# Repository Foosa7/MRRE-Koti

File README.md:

# MRRE-Koti #
* CERN Open Hardware Licence v1.2 
* Original: https://github.com/maplerainresearch/MRR_ESPE

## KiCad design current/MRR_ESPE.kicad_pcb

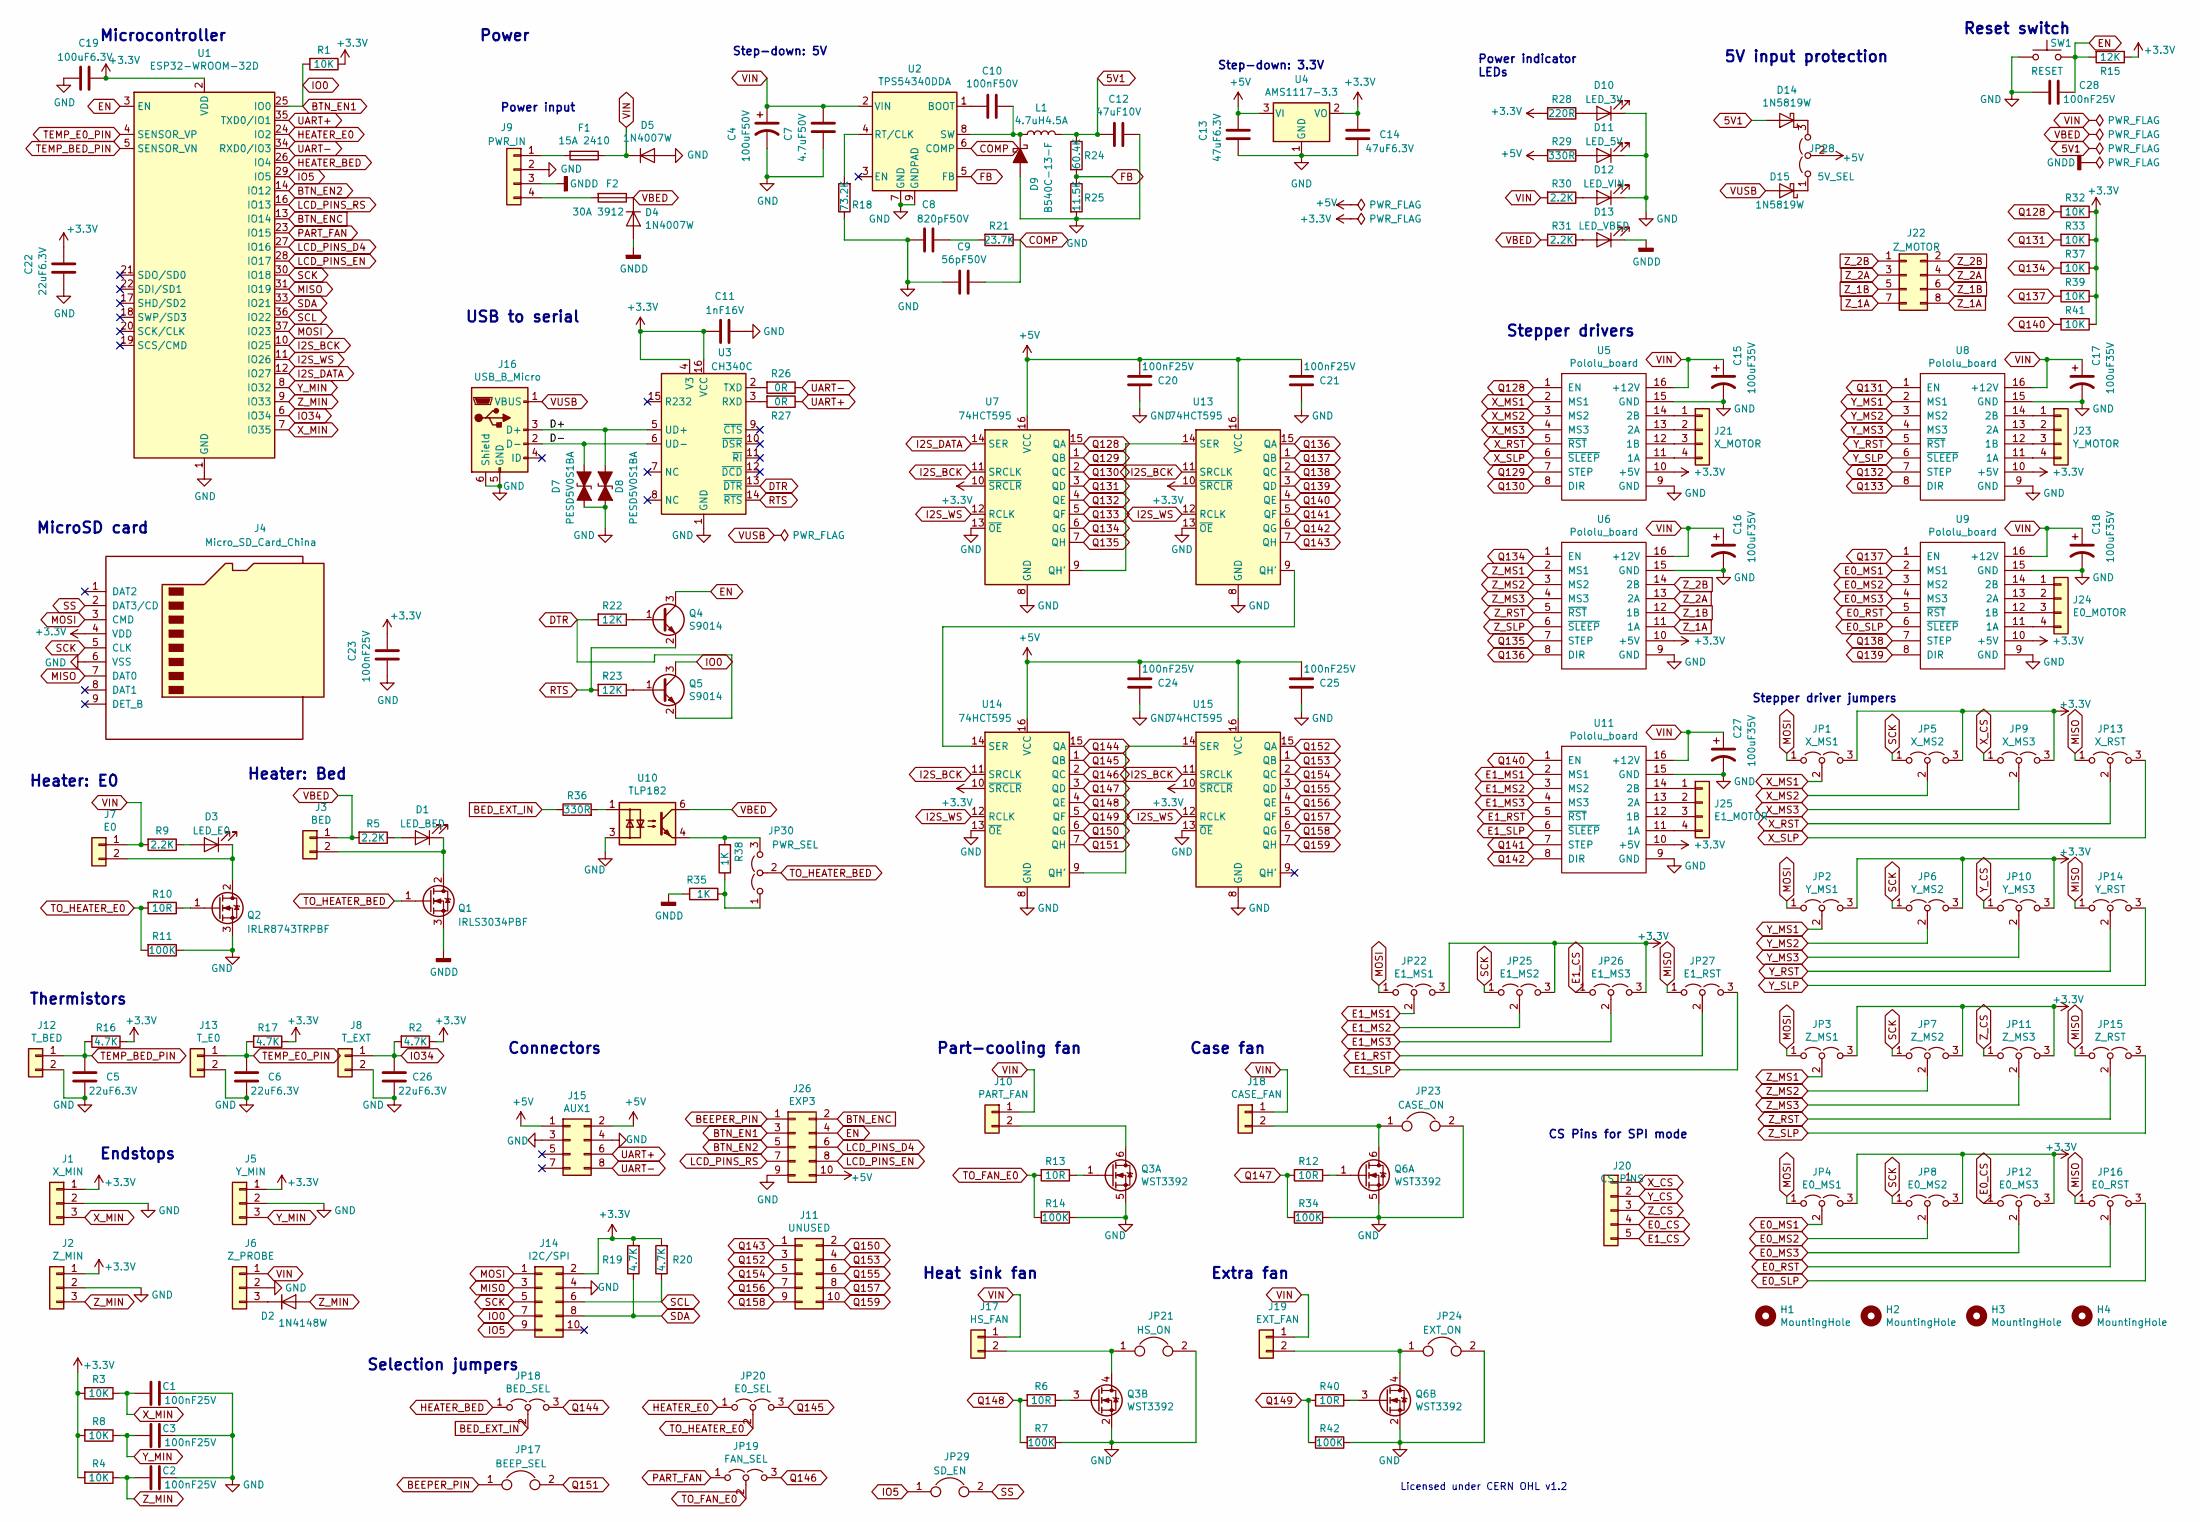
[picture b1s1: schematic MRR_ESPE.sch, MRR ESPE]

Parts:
C1, C2, C3, C20, C21, C23, C24, C25, C28: 100nF25V; C_0805_2012Metric; Mfg part no. 0805B104K250; LCSC Part Number C128353
C4: 100uF50V; CP_Elec_8x10; Mfg part no. VEJ101M1HTR-0810; LCSC Part Number C176665
C5, C6, C22, C26: 22uF6.3V; C_0805_2012Metric; Mfg part no. CL21A226MQQNNNE; LCSC Part Number C5674
C7: 4.7uF50V; C_1206_3216Metric; Mfg part no. CL31B475KBHNFNE; LCSC Part Number C307575
C8: 820pF50V; C_0805_2012Metric; Mfg part no. 0805B821K500CT; LCSC Part Number C152862
C9: 56pF50V; C_0805_2012Metric; Mfg part no. 0805N560J500CT; LCSC Part Number C296102
C10: 100nF50V; C_0805_2012Metric; Mfg part no. GCM21BR71H104KA37L; LCSC Part Number C161260
C11: 1nF16V; C_0805_2012Metric; Mfg part no. 0805B103K500NT; LCSC Part Number C52278
C12: 47uF10V; C_1206_3216Metric; Mfg part no. LMK316BJ476ML-T; LCSC Part Number C92821
C13, C14: 47uF6.3V; C_0805_2012Metric; Mfg part no. JMK212BJ476MG-T; LCSC Part Number C87159
C15, C16, C17, C18, C27: 100uF35V; CP_Elec_6.3x7.7; Mfg part no. CS1V101M-CRE77; LCSC Part Number C97811
C19: 100uF6.3V; C_1206_3216Metric; Mfg part no. CL31A107MQHNNNE; LCSC Part Number C15008
D1: LED_BED; LED_0805; Mfg part no. 17-21SURC/S530-A3/TR8; LCSC Part Number C72037
D2: 1N4148W; D_SOD-123; Mfg part no. 1N4148W; LCSC Part Number C81598
D3: LED_E0; LED_0805; Mfg part no. 17-21SURC/S530-A3/TR8; LCSC Part Number C72037
D4, D5: 1N4007W; D_SOD-123F; Mfg part no. 1N4007W; LCSC Part Number C108803
D7, D8: PESD5V0S1BA; D_SOD-323; Mfg part no. PESD5V0S1BA,115; LCSC Part Number C19224
D9: B540C-13-F; D_SMC; Mfg part no. B540C-13-F; LCSC Part Number C72264
D10: LED_3V; LED_0805; Mfg part no. 17-21SYGC/S530-E2/TR8; LCSC Part Number C73548
D11: LED_5V; LED_0805; Mfg part no. 17-21SYGC/S530-E2/TR8; LCSC Part Number C73548
D12: LED_VIN; LED_0805; Mfg part no. 17-21/BHC-XL2M2TY/3T; LCSC Part Number C72035
D13: LED_VBED; LED_0805; Mfg part no. 17-21/BHC-XL2M2TY/3T; LCSC Part Number C72035
D14, D15: 1N5819W; D_SOD-123; Mfg part no. 1N5819W; LCSC Part Number C169540
F1: 15A 2410; Littelfuse_0451; Mfg part no. 0451015.MRL; LCSC Part Number C44480
F2: 30A 3912; Littelfuse_0456; Mfg part no. 0456030.ER; LCSC Part Number C187558
H1, H2, H3, H4: MountingHole; MountingHole_3.2mm_M3_DIN965
J1: X_MIN; JST_XH_B03B-XH-A_1x03_P2.50mm_Vertical; Mfg part no. B3B-XH-A(LF)(SN); LCSC Part Number C144394
J2: Z_MIN; JST_XH_B03B-XH-A_1x03_P2.50mm_Vertical; Mfg part no. B3B-XH-A(LF)(SN); LCSC Part Number C144394
J3: BED; TerminalBlock_Phoenix_MKDS-3-2-5.08_1x02_P5.08mm_Horizontal; Mfg part no. MKDS3/2-5.08; LCSC Part Number C89120
J4: Micro_SD_Card_China; Koti_uSDcard; Mfg part no. TF-15×15; LCSC Part Number C111196
J5: Y_MIN; JST_XH_B03B-XH-A_1x03_P2.50mm_Vertical; Mfg part no. B3B-XH-A(LF)(SN); LCSC Part Number C144394
J6: Z_PROBE; JST_XH_B03B-XH-A_1x03_P2.50mm_Vertical; Mfg part no. B3B-XH-A(LF)(SN); LCSC Part Number C144394
J7: E0; TerminalBlock_Phoenix_MKDS-1,5-2-5.08_1x02_P5.08mm_Horizont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; Mfg part no. MKDSN1.5/2-5.08; LCSC Part Number C91153
J8: T_EXT; PinHeader_1x02_P2.54mm_Vertical; Mfg part no. C124375; LCSC Part Number C124375
J9: PWR_IN; TerminalBlock_Phoenix_MKDS-3-4-5.08_1x04_P5.08mm_Horizontal; Mfg part no. MKDS3/4-5.08; LCSC Part Number C90087
J10: PART_FAN; PinHeader_1x02_P2.54mm_Vertical; Mfg part no. C124375; LCSC Part Number C124375
J11: UNUSED; PinHeader_2x05_P2.54mm_Vertical; Mfg part no. C124387; LCSC Part Number C124387
J12: T_BED; PinHeader_1x02_P2.54mm_Vertical; Mfg part no. C124375; LCSC Part Number C124375
J13: T_E0; PinHeader_1x02_P2.54mm_Vertical; Mfg part no. C124375; LCSC Part Number C124375
J14: I2C/SPI; PinHeader_2x05_P2.54mm_Vertical; Mfg part no. C124387; LCSC Part Number C124387
J15: AUX1; IDC-Header_2x04_P2.54mm_Vertical; Mfg part no. C9135; LCSC Part Number C9135
J16: USB_B_Micro; USB_Micro-B_Molex-105017-0001; Mfg part no. 105017-0001; LCSC Part Number C136000
J17: HS_FAN; PinHeader_1x02_P2.54mm_Vertical; Mfg part no. C124375; LCSC Part Number C124375
J18: CASE_FAN; PinHeader_1x02_P2.54mm_Vertical; Mfg part no. C124375; LCSC Part Number C124375
J19: EXT_FAN; PinHeader_1x02_P2.54mm_Vertical; Mfg part no. C124375; LCSC Part Number C124375
J20: CS_PINS; PinHeader_1x05_P2.54mm_Vertical; Mfg part no. C124379; LCSC Part Number C124379
J21: X_MOTOR; PinHeader_1x04_P2.54mm_Vertical; Mfg part no. C124378; LCSC Part Number C124378
J22: Z_MOTOR; PinHeader_2x04_P2.54mm_Vertical; Mfg part no. C124386; LCSC Part Number C124386
J23: Y_MOTOR; PinHeader_1x04_P2.54mm_Vertical; Mfg part no. C124378; LCSC Part Number C124378
J24: E0_MOTOR; PinHeader_1x04_P2.54mm_Vertical; Mfg part no. C124378; LCSC Part Number C124378
J25: E1_MOTOR; PinHeader_1x04_P2.54mm_Vertical; Mfg part no. C124378; LCSC Part Number C124378
J26: EXP3; IDC-Header_2x05_P2.54mm_Vertical; Mfg part no. C5665; LCSC Part Number C5665
JP1: X_MS1; PinHeader_1x03_P2.54mm_Vertical; Mfg part no. C124376; LCSC Part Number C124376
JP2: Y_MS1; PinHeader_1x03_P2.54mm_Vertical; Mfg part no. C124376; LCSC Part Number C124376
JP3: Z_MS1; PinHeader_1x03_P2.54mm_Vertical; Mfg part no. C124376; LCSC Part Number C124376
JP4: E0_MS1; PinHeader_1x03_P2.54mm_Vertical; Mfg part no. C124376; LCSC Part Number C124376
JP5: X_MS2; PinHeader_1x03_P2.54mm_Vertical; Mfg part no. C124376; LCSC Part Number C124376
JP6: Y_MS2; PinHeader_1x03_P2.54mm_Vertical; Mfg part no. C124376; LCSC Part Number C124376
JP7: Z_MS2; PinHeader_1x03_P2.54mm_Vertical; Mfg part no. C124376; LCSC Part Number C124376
JP8: E0_MS2; PinHeader_1x03_P2.54mm_Vertical; Mfg part no. C124376; LCSC Part Number C124376
JP9: X_MS3; PinHeader_1x03_P2.54mm_Vertical; Mfg part no. C124376; LCSC Part Number C124376
JP10: Y_MS3; PinHeader_1x03_P2.54mm_Vertical; Mfg part no. C124376; LCSC Part Number C124376
JP11: Z_MS3; PinHeader_1x03_P2.54mm_Vertical; Mfg part no. C124376; LCSC Part Number C124376
JP12: E0_MS3; PinHeader_1x03_P2.54mm_Vertical; Mfg part no. C124376; LCSC Part Number C124376
JP13: X_RST; PinHeader_1x03_P2.54mm_Vertical; Mfg part no. C124376; LCSC Part Number C124376
JP14: Y_RST; PinHeader_1x03_P2.54mm_Vertical; Mfg part no. C124376; LCSC Part Number C124376
JP15: Z_RST; PinHeader_1x03_P2.54mm_Vertical; Mfg part no. C124376; LCSC Part Number C124376
JP16: E0_RST; PinHeader_1x03_P2.54mm_Vertical; Mfg part no. C124376; LCSC Part Number C124376
JP17: BEEP_SEL; PinHeader_1x02_P2.54mm_Vertical; Mfg part no. C124375; LCSC Part Number C124375
JP18: BED_SEL; PinHeader_1x03_P2.54mm_Vertical; Mfg part no. C124376; LCSC Part Number C124376
JP19: FAN_SEL; PinHeader_1x03_P2.54mm_Vertical; Mfg part no. C124376; LCSC Part Number C124376
JP20: E0_SEL; PinHeader_1x03_P2.54mm_Vertical; Mfg part no. C124376; LCSC Part Number C124376
JP21: HS_ON; PinHeader_1x02_P2.54mm_Vertical; Mfg part no. C124375; LCSC Part Number C124375
JP22: E1_MS1; PinHeader_1x03_P2.54mm_Vertical; Mfg part no. C124376; LCSC Part Number C124376
JP23: CASE_ON; PinHeader_1x02_P2.54mm_Vertical; Mfg part no. C124375; LCSC Part Number C124375
JP24: EXT_ON; PinHeader_1x02_P2.54mm_Vertical; Mfg part no. C124375; LCSC Part Number C124375
JP25: E1_MS2; PinHeader_1x03_P2.54mm_Vertical; Mfg part no. C124376; LCSC Part Number C124376
JP26: E1_MS3; PinHeader_1x03_P2.54mm_Vertical; Mfg part no. C124376; LCSC Part Number C124376
JP27: E1_RST; PinHeader_1x03_P2.54mm_Vertical; Mfg part no. C124376; LCSC Part Number C124376
JP28: 5V_SEL; PinHeader_1x03_P2.54mm_Vertical; Mfg part no. C124376; LCSC Part Number C124376
JP29: SD_EN; PinHeader_1x02_P2.54mm_Vertical; Mfg part no. C124375; LCSC Part Number C124375
JP30: PWR_SEL; PinHeader_1x03_P2.54mm_Vertical; Mfg part no. C124376; LCSC Part Number C124376
L1: 4.7uH4.5A; SMMS0530; Mfg part no. SMMS0530-4R7M; LCSC Part Number C181722
Q1: IRLS3034PBF; TO-263-2
Q2: IRLR8743TRPBF; TO-252-2
Q3, Q6: WST3392; SOT-23-6_Handsoldering; Mfg part no. WST3392; LCSC Part Number C148366
Q4, Q5: S9014; SOT-23; Mfg part no. S9014; LCSC Part Number C181164
R1, R3, R4, R8, R32, R33, R37, R39, R41: 10K; R_0805_2012Metric; Mfg part no. 0805W8F1002T5E; LCSC Part Number C38522
R2, R16, R17, R19, R20: 4.7K; R_0805_2012Metric; Mfg part no. 0805W8F4701T5E; LCSC Part Number C17673
R5, R9, R30, R31: 2.2K; R_0805_2012Metric; Mfg part no. 0805W8F2201T5E; LCSC Part Number C17520
R6, R10, R12, R13, R40: 10R; R_0805_2012Metric; Mfg part no. 0805W8F100JT5E; LCSC Part Number C17415
R7, R11, R14, R34, R42: 100K; R_0805_2012Metric; Mfg part no. 0805W8F1003T5E; LCSC Part Number C149504
R15, R22, R23: 12K; R_0805_2012Metric; Mfg part no. 0805W8F1202T5E; LCSC Part Number C17444
R18: 73.2K; R_0805_2012Metric; Mfg part no. WR08X7322FTL; LCSC Part Number C170958
R21: 23.7K; R_0805_2012Metric; Mfg part no. WR08X2372FTL; LCSC Part Number C170848
R24: 60.4K; R_0805_2012Metric; Mfg part no. RC0805FR-0760K4L; LCSC Part Number C273994
R25: 11.5K; R_0805_2012Metric; Mfg part no. 0805W8F1152T5E; LCSC Part Number C17418
R26, R27: 0R; R_0805_2012Metric; Mfg part no. 0805W8F0000T5E; LCSC Part Number C17477
R28: 220R; R_0805_2012Metric; Mfg part no. 0805W8F2200T5E; LCSC Part Number C17557
R29, R36: 330R; R_0805_2012Metric; Mfg part no. 0805W8F3300T5E; LCSC Part Number C17630
R35, R38: 1K; R_0805_2012Metric; Mfg part no. 0805W8F1001T5E; LCSC Part Number C17513
SW1: RESET; 6x6mmTactileSwitch; Mfg part no. K2-6639SP-C4SC-04; LCSC Part Number C83206
U1: ESP32-WROOM-32D; ESP32-WROOM-32; Mfg part no. ESP32-WROOM-32; LCSC Part Number C95209
U2: TPS54340DDA; TI_SO-PowerPAD-8_ThermalVias; Mfg part no. TPS54340DDAR; LCSC Part Number C45886
U3: CH340C; SOIC-16_3.9x9.9mm_P1.27mm; Mfg part no. CH340C; LCSC Part Number C84681
U4: AMS1117-3.3; SOT-223-3_TabPin2; Mfg part no. AMS1117-3.3; LCSC Part Number C6186
U5, U6, U8, U9, U11: Pololu_board; Pololu_Breakout-16_15.2x20.3mm; Mfg part no. x2; LCSC Part Number C27438
U7, U13, U14, U15: 74HCT595; TSSOP-16_4.4x5mm_P0.65mm; Mfg part no. MC74HCT595ADTR2G; LCSC Part Number C152276
U10: TLP182; MFSOP6-4_4.4x3.6mm_P1.27mm; Mfg part no. TLP182(GB-TPL,E; LCSC Part Number C96457

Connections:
5V1: C12.2, D14.2 (A), L1.2, R24.1
+3V3: C11.2, C14.1, C19.1, C22.1, C23.1, J1.1, J2.1, J4.4 (VDD), J5.1, J14.2, JP1.3 (B), JP2.3 (B), JP3.3 (B), JP4.3 (B), JP5.3 (B), JP6.3 (B), JP7.3 (B), JP8.3 (B), JP9.3 (B), JP10.3 (B), JP11.3 (B), JP12.3 (B), JP22.3 (B), JP25.3 (B), JP26.3 (B), R1.1, R2.1, R3.2, R4.2, R8.2, R15.1, R16.1, R17.1, R19.2, R20.2, R28.2, R32.1, R33.1, R37.1, R39.1, R41.1, U1.2 (VDD), U3.4 (V3), U3.16 (VCC), U4.2 (VO), U5.10 (+5V), U6.10 (+5V), U7.10 (~SRCLR), U8.10 (+5V), U9.10 (+5V), U11.10 (+5V), U13.10 (~SRCLR), U14.10 (~SRCLR), U15.10 (~SRCLR)
+5V: C13.1, C20.2, C21.2, C24.2, C25.2, J15.1, J15.2, J26.10, JP28.2 (C), R29.2, U4.3 (VI), U7.16 (VCC), U13.16 (VCC), U14.16 (VCC), U15.16 (VCC)
/D+: D8.1 (A1), J16.3 (D+), U3.5 (UD+)
/D-: D7.1 (A1), J16.2 (D-), U3.6 (UD-)
BED_EXT_IN: JP18.2 (C), R36.1
BEEPER_PIN: J26.1, JP17.1
BTN_EN1: J14.7, J26.3, Q5.3 (C), R1.2, U1.25 (IO0)
BTN_EN2: J26.5, U1.14 (IO12)
BTN_ENC: J26.2, U1.13 (IO14)
COMP: C9.1, R21.1, U2.6 (COMP)
DTR: Q5.2 (E), R22.2, U3.13 (~DTR)
E0_CS: J20.4, JP12.1 (A)
E0_MS1: JP4.2 (C), U9.2 (MS1)
E0_MS2: JP8.2 (C), U9.3 (MS2)
E0_MS3: JP12.2 (C), U9.4 (MS3)
E0_RST: JP16.2 (C), U9.5 (~RST)
E0_SLP: JP16.3 (B), U9.6 (~SLEEP)
E1_CS: J20.5, JP26.1 (A)
E1_MS1: JP22.2 (C), U11.2 (MS1)
E1_MS2: JP25.2 (C), U11.3 (MS2)
E1_MS3: JP26.2 (C), U11.4 (MS3)
E1_RST: JP27.2 (C), U11.5 (~RST)
E1_SLP: JP27.3 (B), U11.6 (~SLEEP)
EN: C28.1, J26.4, Q4.3 (C), R15.2, SW1.2, U1.3 (EN)
FB: R24.2, R25.1, U2.5 (FB)
GND: C1.1, C2.1, C3.1, C4.2, C5.1, C6.1, C7.1, C8.2, C9.2, C11.1, C12.1, C13.2, C14.2, C15.2, C16.2, C17.2, C18.2, C19.2, C20.1, C21.1, C22.2, C23.2, C24.1, C25.1, C26.1, C27.2, C28.2, D5.2 (A), D7.2 (A2), D8.2 (A2), D9.2 (A), D10.1 (K), D11.1 (K), D12.1 (K), J1.2, J2.2, J4.6 (VSS), J5.2, J6.2, J8.2, J9.2, J12.2, J13.2, J14.4, J15.3, J15.4, J16.5 (GND), J16.6 (Shield), J26.9, JP21.2, JP23.2, JP24.2, Q2.3 (S), Q3.2 (S), Q3.5 (S), Q6.2 (S), Q6.5 (S), R7.1, R11.1, R14.1, R18.1, R25.2, R34.1, R42.1, SW1.1, U1.1 (GND), U1.15 (GND), U1.38 (GND), U1.39 (GND), U2.7 (GND), U2.9 (GNDPAD), U3.1 (GND), U4.1 (GND), U5.9 (GND), U5.15 (GND), U6.9 (GND), U6.15 (GND), U7.8 (GND), U7.13 (~OE), U8.9 (GND), U8.15 (GND), U9.9 (GND), U9.15 (GND), U10.3, U11.9 (GND), U11.15 (GND), U13.8 (GND), U13.13 (~OE), U14.8 (GND), U14.13 (~OE), U15.8 (GND), U15.13 (~OE)
GNDD: D4.2 (A), D13.1 (K), J9.3, Q1.3 (S), R35.1
HEATER_BED: JP18.1 (A), U1.26 (IO4)
HEATER_E0: JP20.1 (A), U1.24 (IO2)
I2S_BCK: U1.10 (IO25), U7.11 (SRCLK), U13.11 (SRCLK), U14.11 (SRCLK), U15.11 (SRCLK)
I2S_DATA: U1.12 (IO27), U7.14 (SER)
I2S_WS: U1.11 (IO26), U7.12 (RCLK), U13.12 (RCLK), U14.12 (RCLK), U15.12 (RCLK)
IO5: J14.9, JP29.1, U1.29 (IO5)
IO34: C26.2, J8.1, R2.2, U1.6 (IO34)
LCD_PINS_D4: J26.6, U1.27 (IO16)
LCD_PINS_EN: J26.8, U1.28 (IO17)
LCD_PINS_RS: J26.7, U1.16 (IO13)
MISO: J4.7 (DAT0), J14.3, JP13.1 (A), JP14.1 (A), JP15.1 (A), JP16.1 (A), JP27.1 (A), U1.31 (IO19)
MOSI: J4.3 (CMD), J14.1, JP1.1 (A), JP2.1 (A), JP3.1 (A), JP4.1 (A), JP22.1 (A), U1.37 (IO23)
unnamed: C8.1, R21.2
unnamed: C10.1, D9.1 (K), L1.1, U2.8 (SW)
unnamed: C10.2, U2.1 (BOOT)
unnamed: D1.1 (K), J3.2, Q1.2 (D)
unnamed: D1.2 (A), R5.1
unnamed: D2.1 (K), J6.3
unnamed: D3.1 (K), J7.2, Q2.2 (D)
unnamed: D3.2 (A), R9.1
unnamed: D10.2 (A), R28.1
unnamed: D11.2 (A), R29.1
unnamed: D12.2 (A), R30.1
unnamed: D13.2 (A), R31.1
unnamed: D14.1 (K), JP28.3 (B)
unnamed: D15.1 (K), JP28.1 (A)
unnamed: F1.2, J9.1
unnamed: F2.2, J9.4
unnamed: J10.2, Q3.6 (D)
unnamed: J17.2, JP21.1, Q3.4 (D)
unnamed: J18.2, JP23.1, Q6.6 (D)
unnamed: J19.2, JP24.1, Q6.4 (D)
unnamed: J21.1, U5.14 (2B)
unnamed: J21.2, U5.13 (2A)
unnamed: J21.3, U5.12 (1B)
unnamed: J21.4, U5.11 (1A)
unnamed: J23.1, U8.14 (2B)
unnamed: J23.2, U8.13 (2A)
unnamed: J23.3, U8.12 (1B)
unnamed: J23.4, U8.11 (1A)
unnamed: J24.1, U9.14 (2B)
unnamed: J24.2, U9.13 (2A)
unnamed: J24.3, U9.12 (1B)
unnamed: J24.4, U9.11 (1A)
unnamed: J25.1, U11.14 (2B)
unnamed: J25.2, U11.13 (2A)
unnamed: J25.3, U11.12 (1B)
unnamed: J25.4, U11.11 (1A)
unnamed: JP30.1 (A), R35.2, R38.1
unnamed: JP30.3 (B), R38.2, U10.4
unnamed: Q2.1 (G), R10.1
unnamed: Q3.1 (G), R13.1
unnamed: Q3.3 (G), R6.1
unnamed: Q4.1 (B), R22.1
unnamed: Q5.1 (B), R23.1
unnamed: Q6.1 (G), R12.1
unnamed: Q6.3 (G), R40.1
unnamed: R18.2, U2.4 (RT/CLK)
unnamed: R26.2, U3.2 (TXD)
unnamed: R27.2, U3.3 (RXD)
unnamed: R36.2, U10.1
unnamed: U13.9 (QH'), U14.14 (SER)
unnamed: U7.9 (QH'), U13.14 (SER)
unnamed: U14.9 (QH'), U15.14 (SER)
PART_FAN: JP19.1 (A), U1.23 (IO15)
Q128: R32.2, U5.1 (EN), U7.15 (QA)
Q129: U5.7 (STEP), U7.1 (QB)
Q130: U5.8 (DIR), U7.2 (QC)
Q131: R33.2, U7.3 (QD), U8.1 (EN)
Q132: U7.4 (QE), U8.7 (STEP)
Q133: U7.5 (QF), U8.8 (DIR)
Q134: R37.2, U6.1 (EN), U7.6 (QG)
Q135: U6.7 (STEP), U7.7 (QH)
Q136: U6.8 (DIR), U13.15 (QA)
Q137: R39.2, U9.1 (EN), U13.1 (QB)
Q138: U9.7 (STEP), U13.2 (QC)
Q139: U9.8 (DIR), U13.3 (QD)
Q140: R41.2, U11.1 (EN), U13.4 (QE)
Q141: U11.7 (STEP), U13.5 (QF)
Q142: U11.8 (DIR), U13.6 (QG)
Q143: J11.1, U13.7 (QH)
Q144: JP18.3 (B), U14.15 (QA)
Q145: JP20.3 (B), U14.1 (QB)
Q146: JP19.3 (B), U14.2 (QC)
Q147: R12.2, R34.2, U14.3 (QD)
Q148: R6.2, R7.2, U14.4 (QE)
Q149: R40.2, R42.2, U14.5 (QF)
Q150: J11.2, U14.6 (QG)
Q151: JP17.2, U14.7 (QH)
Q152: J11.3, U15.15 (QA)
Q153: J11.4, U15.1 (QB)
Q154: J11.5, U15.2 (QC)
Q155: J11.6, U15.3 (QD)
Q156: J11.7, U15.4 (QE)
Q157: J11.8, U15.5 (QF)
Q158: J11.9, U15.6 (QG)
Q159: J11.10, U15.7 (QH)
RTS: Q4.2 (E), R23.2, U3.14 (~RTS)
SCK: J4.5 (CLK), J14.5, JP5.1 (A), JP6.1 (A), JP7.1 (A), JP8.1 (A), JP25.1 (A), U1.30 (IO18)
SCL: J14.6, R20.1, U1.36 (IO22)
SDA: J14.8, R19.1, U1.33 (IO21)
SS: J4.2 (DAT3/CD), JP29.2
TEMP_BED_PIN: C5.2, J12.1, R16.2, U1.5 (SENSOR_VN)
TEMP_E0_PIN: C6.2, J13.1, R17.2, U1.4 (SENSOR_VP)
TO_FAN_E0: JP19.2 (C), R13.2, R14.2
TO_HEATER_BED: JP30.2 (C), Q1.1 (G)
TO_HEATER_E0: JP20.2 (C), R10.2, R11.2
UART+: J15.6, R27.1, U1.35 (TXD0/IO1)
UART-: J15.8, R26.1, U1.34 (RXD0/IO3)
VBED: D4.1 (K), F2.1, J3.1, R5.2, R31.2, U10.6
VIN: C4.1, C7.2, C15.1, C16.1, C17.1, C18.1, C27.1, D5.1 (K), F1.1, J6.1, J7.1, J10.1, J17.1, J18.1, J19.1, R9.2, R30.2, U2.2 (VIN), U5.16 (+12V), U6.16 (+12V), U8.16 (+12V), U9.16 (+12V), U11.16 (+12V)
VUSB: D15.2 (A), J16.1 (VBUS)
X_CS: J20.1, JP9.1 (A)
X_MIN: C1.2, J1.3, R3.1, U1.7 (IO35)
X_MS1: JP1.2 (C), U5.2 (MS1)
X_MS2: JP5.2 (C), U5.3 (MS2)
X_MS3: JP9.2 (C), U5.4 (MS3)
X_RST: JP13.2 (C), U5.5 (~RST)
X_SLP: JP13.3 (B), U5.6 (~SLEEP)
Y_CS: J20.2, JP10.1 (A)
Y_MIN: C3.2, J5.3, R8.1, U1.8 (IO32)
Y_MS1: JP2.2 (C), U8.2 (MS1)
Y_MS2: JP6.2 (C), U8.3 (MS2)
Y_MS3: JP10.2 (C), U8.4 (MS3)
Y_RST: JP14.2 (C), U8.5 (~RST)
Y_SLP: JP14.3 (B), U8.6 (~SLEEP)
Z_1A: J22.7, J22.8, U6.11 (1A)
Z_1B: J22.5, J22.6, U6.12 (1B)
Z_2A: J22.3, J22.4, U6.13 (2A)
Z_2B: J22.1, J22.2, U6.14 (2B)
Z_CS: J20.3, JP11.1 (A)
Z_MIN: C2.2, D2.2 (A), J2.3, R4.1, U1.9 (IO33)
Z_MS1: JP3.2 (C), U6.2 (MS1)
Z_MS2: JP7.2 (C), U6.3 (MS2)
Z_MS3: JP11.2 (C), U6.4 (MS3)
Z_RST: JP15.2 (C), U6.5 (~RST)
Z_SLP: JP15.3 (B), U6.6 (~SLEEP)

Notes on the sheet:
Microcontroller
MicroSD card
Power
Step-down: 5V
Step-down: 3.3V
Power indicator LEDs
Power input
USB to serial
5V input protection
Heater: Bed
Heater: E0
Part-cooling fan
Stepper drivers
Thermistors
Endstops
Reset switch
Connectors
Stepper driver jumpers
CS Pins for SPI mode
Licensed under CERN OHL v1.2
Case fan
Heat sink fan
Extra fan
Selection jumpers

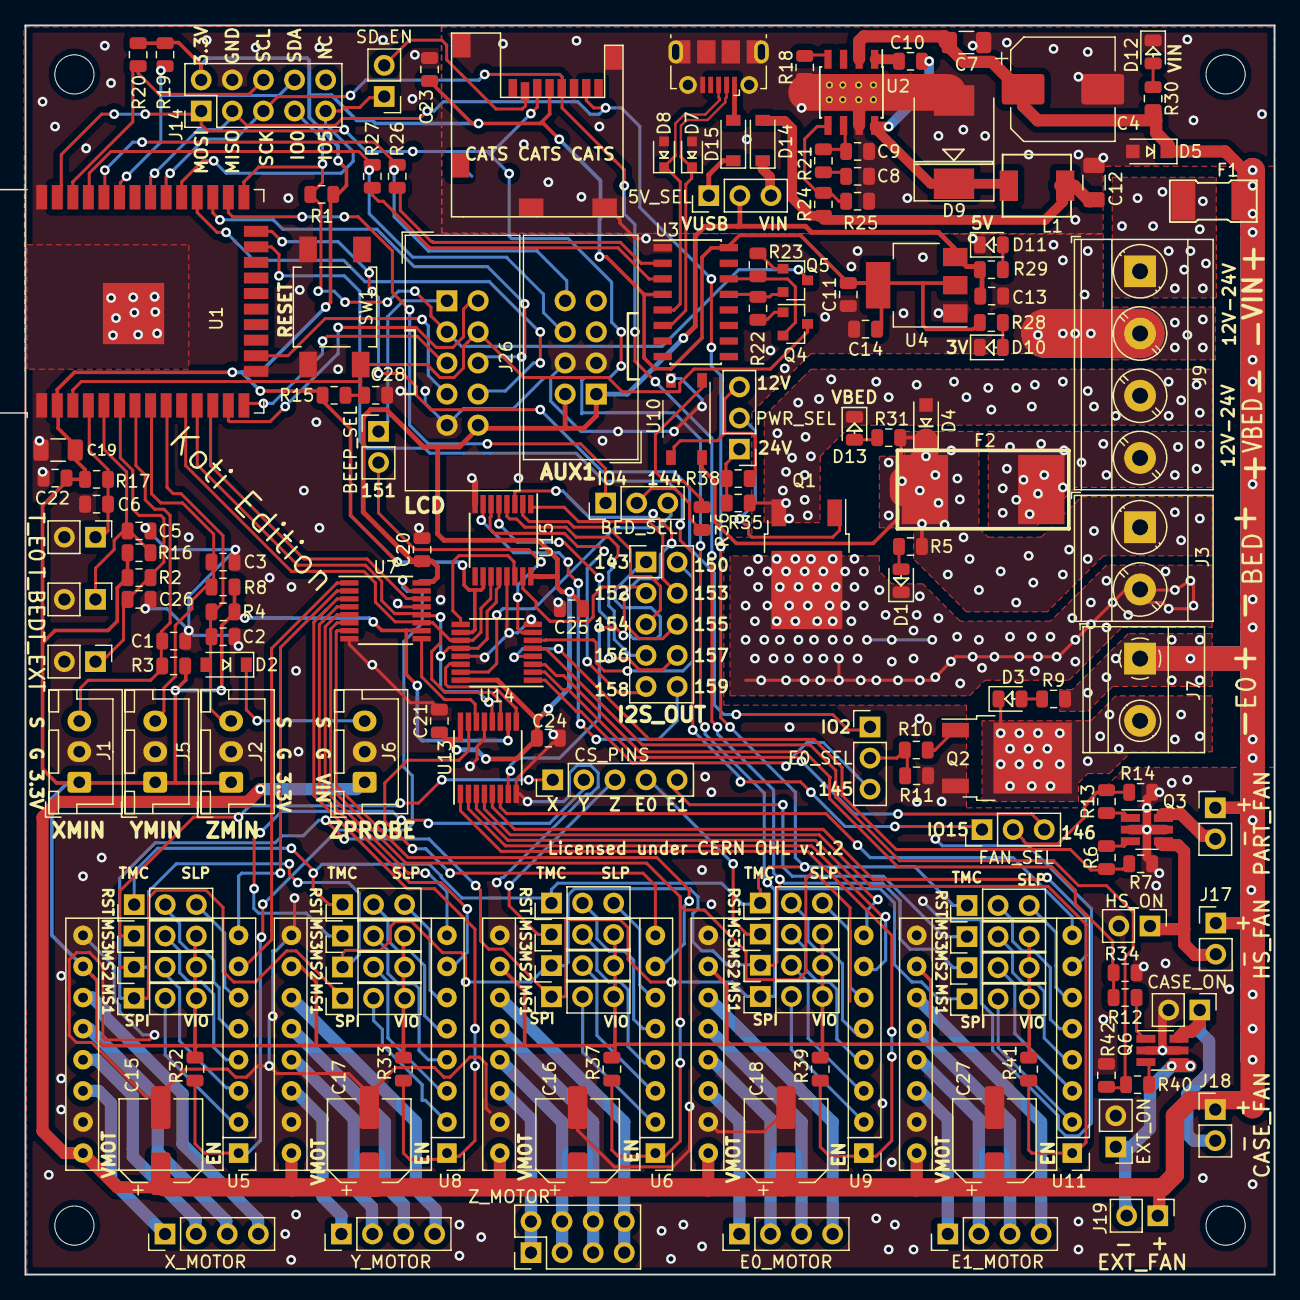
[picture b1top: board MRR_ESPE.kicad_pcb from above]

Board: 2 copper layers, 102.0 x 102.0 mm, 168 parts (0 on the bottom side), 165 nets.
